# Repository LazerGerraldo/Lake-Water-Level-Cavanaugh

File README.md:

# Lake-Water-Level-Cavanaugh

I began by seting up the DS18B20 temperature sensor with the ESP8266 shown in the TempSensor8266.ino file. 
After gaining comfort with the ESP8266 and how it differs from an Arduino Nano or Arduino Uno I then followed [the tutorial by Random Nerd Tutorials](https://randomnerdtutorials.com/esp32-esp8266-publish-sensor-readings-to-google-sheets/)  to setup measurement recordings using Google Sheets.

Along the way I was able to combine what I knew about the temperature sensor and the above Google Sheets example and recorded temperatures. That quickly became another project for my aquarium in monitoring the temperature throughout the day. Back to the lake level project. One important thing to note was the need to connect the RST pin to GPIO 16 on the ESP8266 after programming to enable the `
ESP.deepSleep()` cycle. This was a new thing for me and the [article here](https://randomnerdtutorials.com/esp8266-deep-sleep-with-arduino-ide/) goes into more depth.

I received the HC-SR04 Ultrasonic Distance sensor and took a step back. I have found that its important to not pile too much into a project at one time without any opportunity for debugging and solving unexpected problems. With that I moved back to the TempSensor8266.ino file and copied that over to a new project SonarTemp8266.ino, and made sure the sensor interface with the ESP8266 works. I followed the [guide by Makerguides.com here](https://www.makerguides.com/jsn-sr04t-arduino-tutorial/)

Learned that D2 pin does not mean pin 2, in fact it correlates to 4 in the Arduino IDE. I followed the [image here](https://www.electronicwings.com/nodemcu/nodemcu-gpio-with-arduino-ide). The GPIO pin number matters over the digital pin number. 

Here is the datasheet for the [HC-SR04 Ultrasonic Distance sensor](https://www.makerguides.com/wp-content/uploads/2019/02/HCSR04-Datasheet.pdf)

I encountered a problem with the baud rate or symbol rate that the ESP8266 uses for the temperature sensor is different than that of the sonar sensor. The sonar sensor operates at 9600 baud while the temperature sensor examples that I was working off of used 115200. This became quite an obstacle for me as using two separate baud rates on a single device depends on the hardware available. My solution was picking the more standard baud of 9600 as I learned the temperature sensor actually works at both rates. This solution is shown in the SonarTemp.ino.

I got the two sensors working and sending outputs that looked like this 
```` 
22.13ºC
71.82ºF
Distance = 28.34 in
```` 
So awesome! 

Using a tape measure and a cardboard box, I placed the box at the end of the tape measure and moved the sonar sensor along the tape measure taking note of the difference in length in the measured distance and the actual length. An adjustment of 1.17 in was added to the output distance value. 

The sonar sensor had a bit of an angle to the  direction of propagation. As a verification of distance measurements and their accuracy, I measured the distance from the hardwood floor, to the bottom edge of the table top, where the sensor would rest at 28.4 in. The measured distance from sensor to floor came in at 28.34 in, a 0.06 in difference I can live with.

With both major sensing components working synchronously, I moved on to outputting measurements to the Google Sheets document. 

Moved Echo pin on the HC-SR04 from GPPIO pin 0 to 10, as pin 0 has to do with the FLASH function of the ESP8266 and that interfered with the uploading and flashing of new code. 

To get the resource variable from [Webhooks](https://ifttt.com/maker_webhooks) and place the resource variable in my code. Mine was something like `"/trigger/lake_water_level/with/key/nAZjOphL3d-1A7gTlNSrxMJdmqy3"`

Field testing was a success, the Wi-Fi range of ~75ft worked. Had a hard time after the initial testing phase in the field with the program rebooting after power loss. I followed the [ESP8266 Pinout Reference](https://randomnerdtutorials.com/esp8266-pinout-reference-gpios/) guide here and determined the pins I had connected sensors to were causing a fail in reboot. I was using GPIO0 and GPIO2 both of which cause boot to fail when pulled low due to their connection to the HC-SR04. To solve the booting issue, the Echo pin moved to GPIO12 and the Trig pin to GPIO14 as both of those GPIO ports were recommended by the ESP8266 Pinout Reference webpage. That solved the problem for me. 

The example code that I was working with clocked out after five failed WiFi connection attempts. Since this project does not take into consideration the amount of power used, nor any signal interference that may be created, an infinite loop of connection to WiFi was needed. 

<details>
  <summary>WiFi Connection Loop Code Change</summary>

    ````
    while(!!!client.connect(server, 80)) { // keep trying to connect to WiFi until connection is made
        Serial.print(".");
    }
    ````
    
</details>

The final schematic of the data logger device. 

It actually took me two attempts at making a PCB, this was my first time and I did expect something like this to happen. 
I used the given KiCad footprints and did not discover until I was wiring up that I had picked the incorrect footprint for the female pin headers. I had 2.54mm female pin headers on hand, and the PCB holes were much smaller. Not a problem, there were a few other design changes that I wished to make and it all worked out for the best. You can see in the picture below some of the changes I made to the PCB, the smaller board was the first PCB.

<details>
  <summary>PCB Comparison</summary>

</details>

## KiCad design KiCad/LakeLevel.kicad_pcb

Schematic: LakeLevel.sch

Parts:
DS18B20: TBL003-254-03GR-2OR; CUI_TBL003-254-03GR-2OR
J1: Conn_01x05_Female; PinHeader_1x05_P2.54mm_Vertical
R1: 4.7k; R_Axial_DIN0204_L3.6mm_D1.6mm_P7.62mm_Horizontal
U1: NodeMCU1.0(ESP-12E); ESP12F-Devkit-V3

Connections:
/DQ: DS18B20.2_A (2), DS18B20.2_B (2), R1.2, U1.28
/GND: DS18B20.1_A (1), DS18B20.1_B (1), J1.4, U1.17, U1.24
/RX_Trig: J1.2, U1.23
/TX_Echo: J1.3, U1.22
/VDD: DS18B20.3_A (3), DS18B20.3_B (3), J1.1, R1.1, U1.25

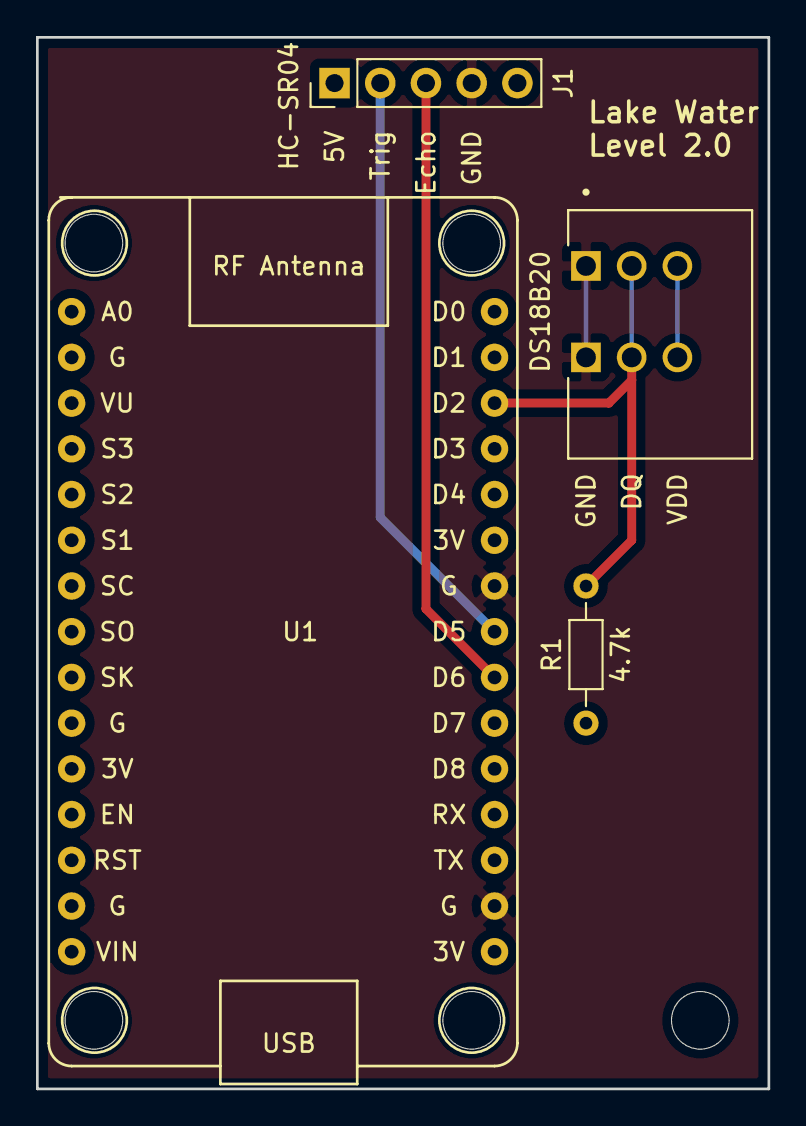
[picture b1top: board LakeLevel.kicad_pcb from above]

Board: 2 copper layers, 40.6 x 58.4 mm, 4 parts (0 on the bottom side), 5 nets.

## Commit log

2021-04-07 initial breadboarding and added test files
2021-06-14 KiCad Files and readme updates
2021-06-14 readme and picture update
2021-06-14 readme updates
2021-06-14 link setup
